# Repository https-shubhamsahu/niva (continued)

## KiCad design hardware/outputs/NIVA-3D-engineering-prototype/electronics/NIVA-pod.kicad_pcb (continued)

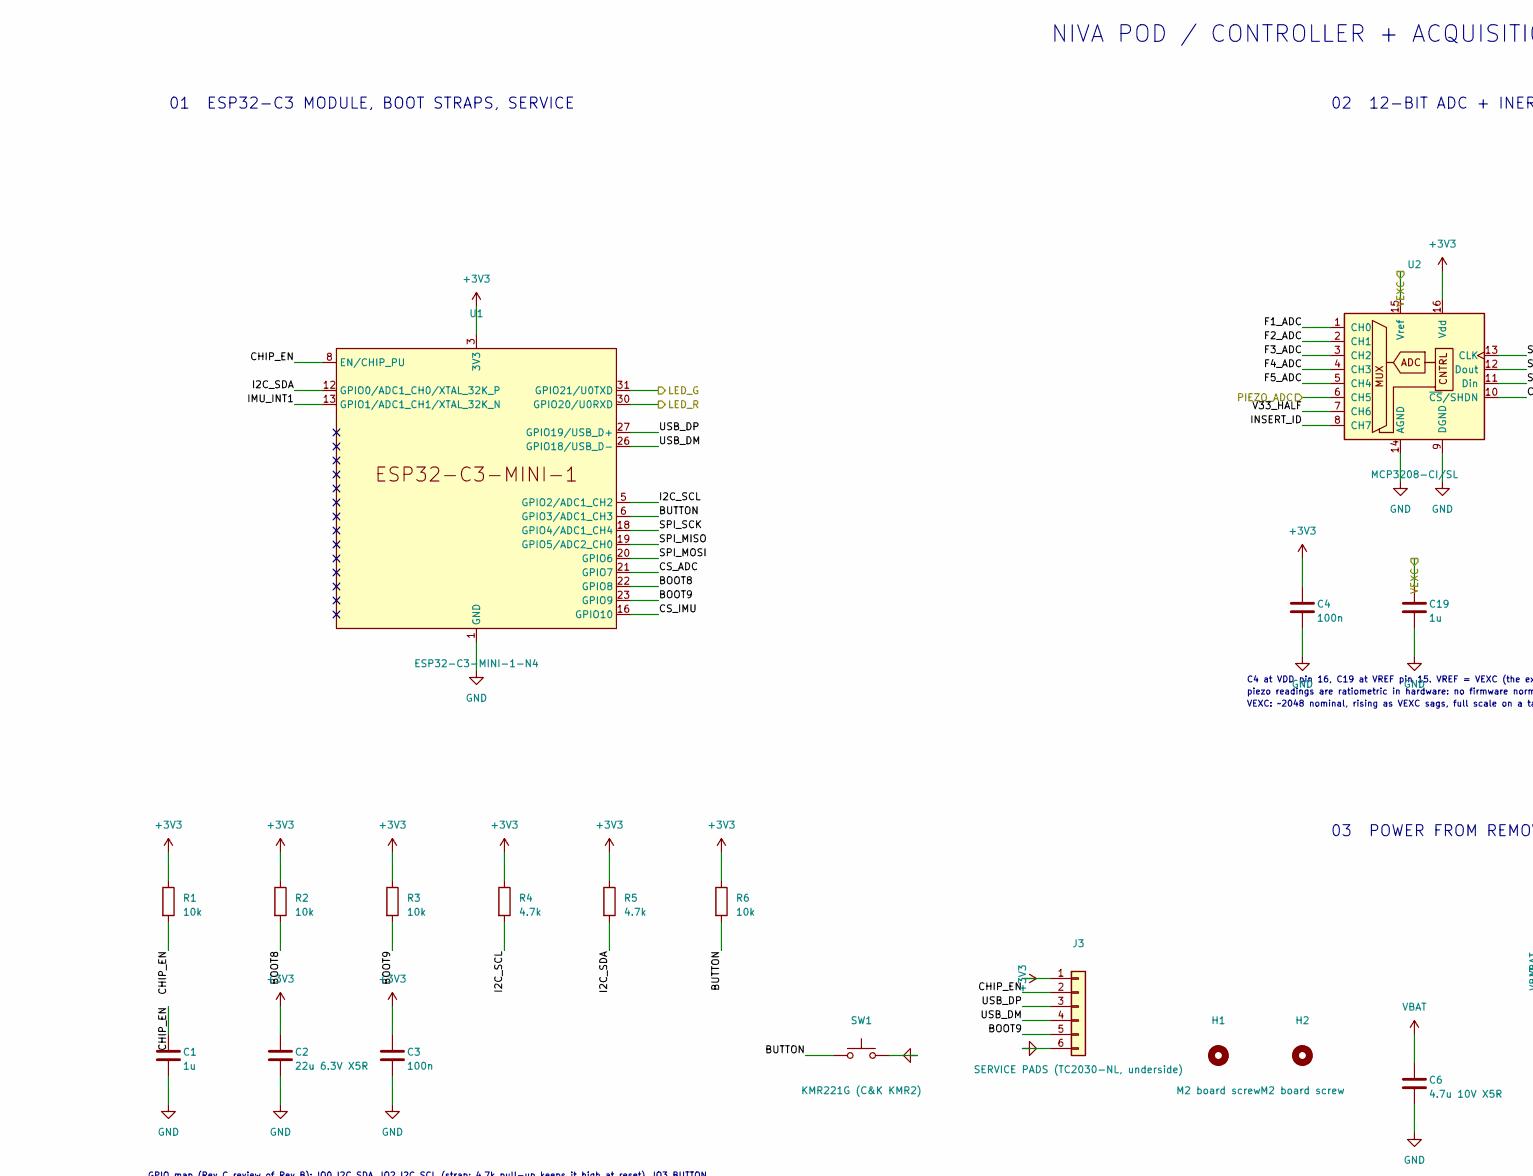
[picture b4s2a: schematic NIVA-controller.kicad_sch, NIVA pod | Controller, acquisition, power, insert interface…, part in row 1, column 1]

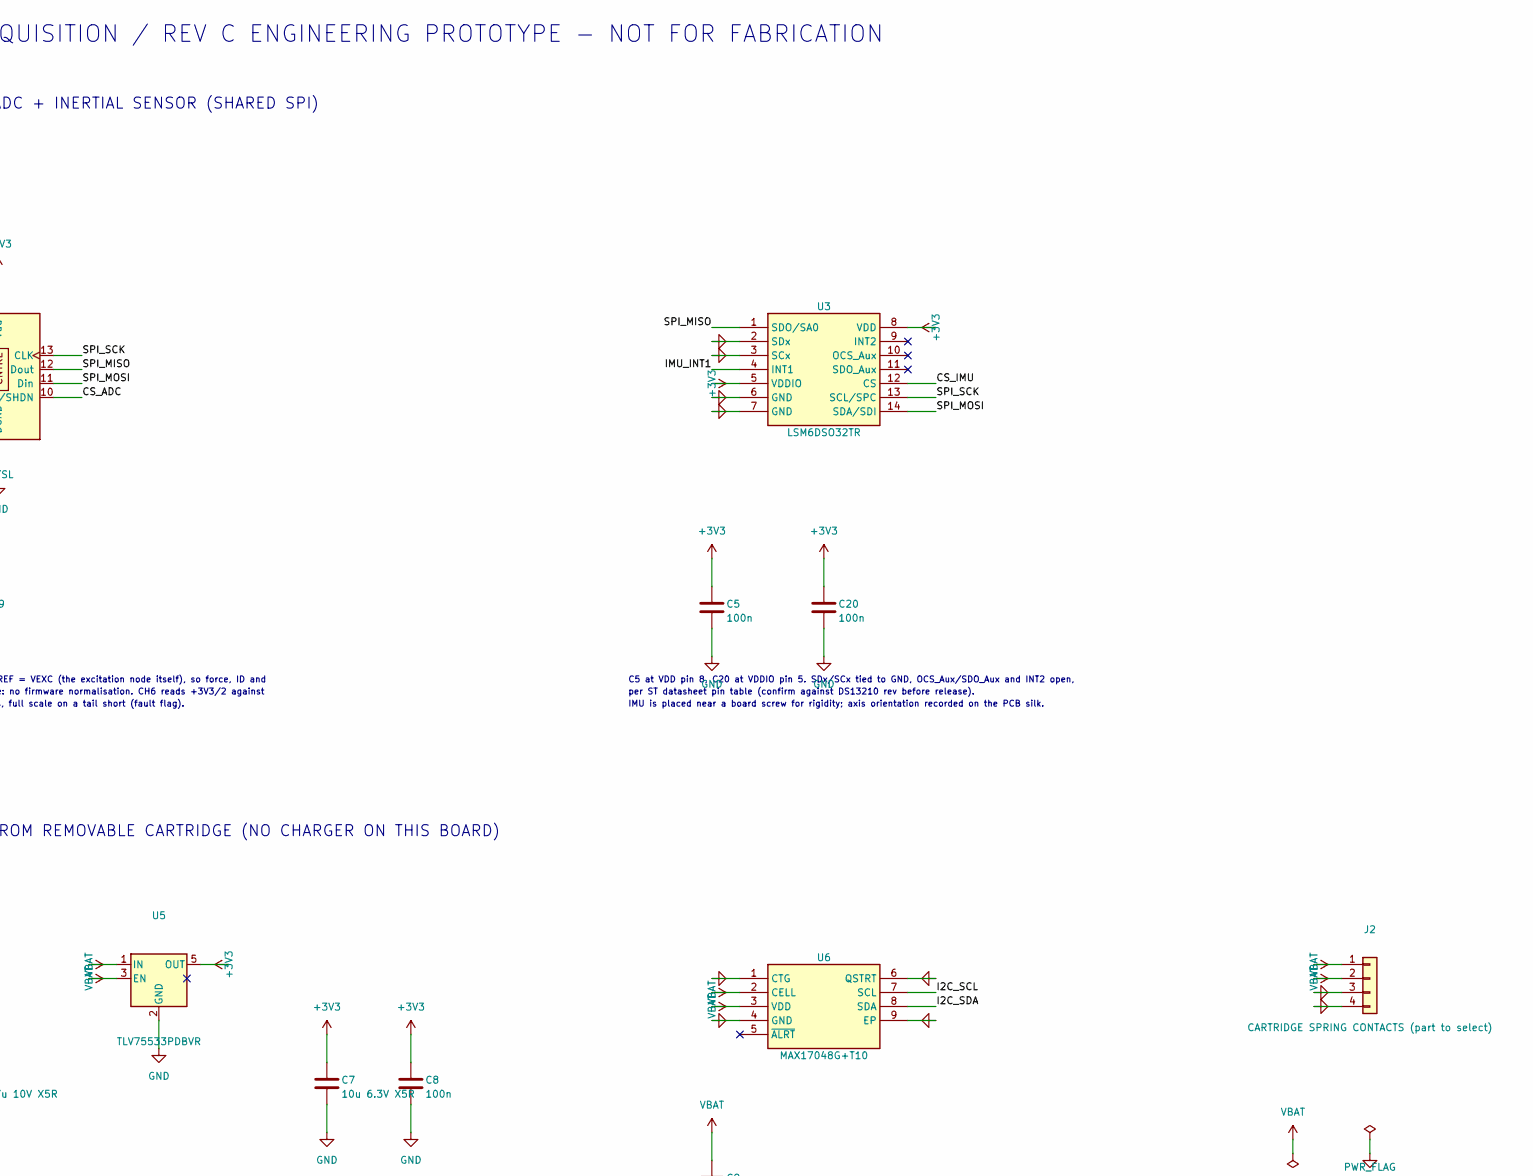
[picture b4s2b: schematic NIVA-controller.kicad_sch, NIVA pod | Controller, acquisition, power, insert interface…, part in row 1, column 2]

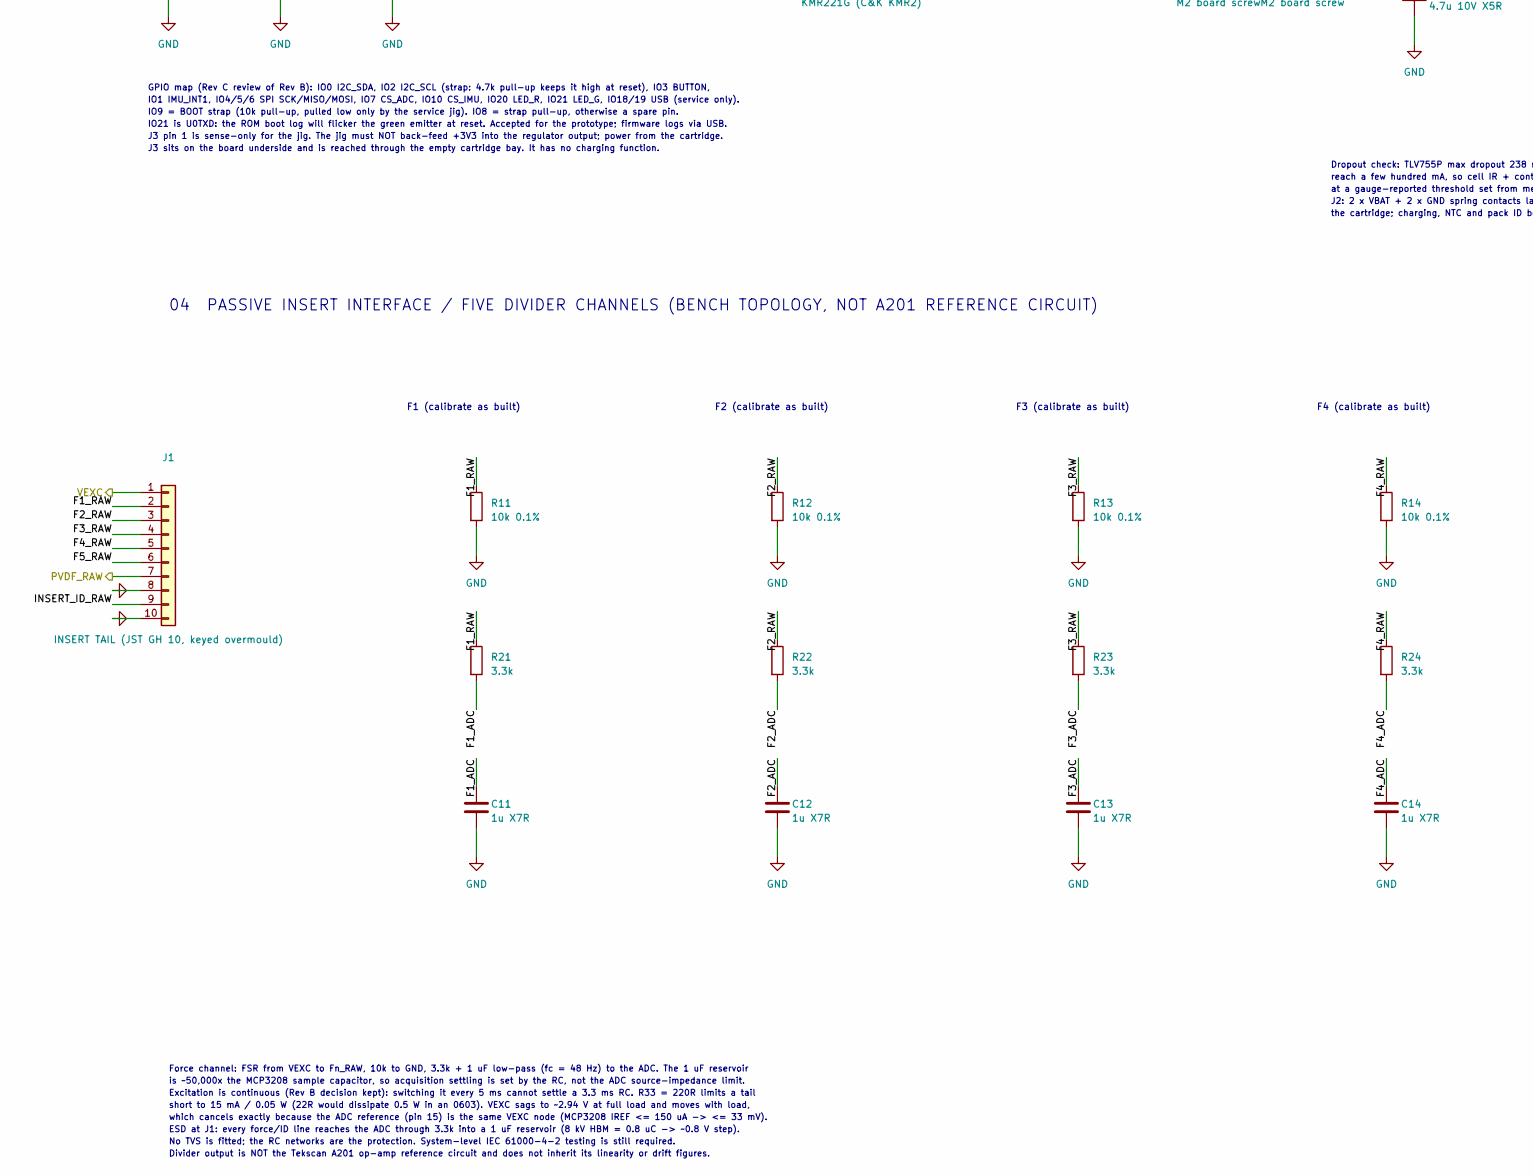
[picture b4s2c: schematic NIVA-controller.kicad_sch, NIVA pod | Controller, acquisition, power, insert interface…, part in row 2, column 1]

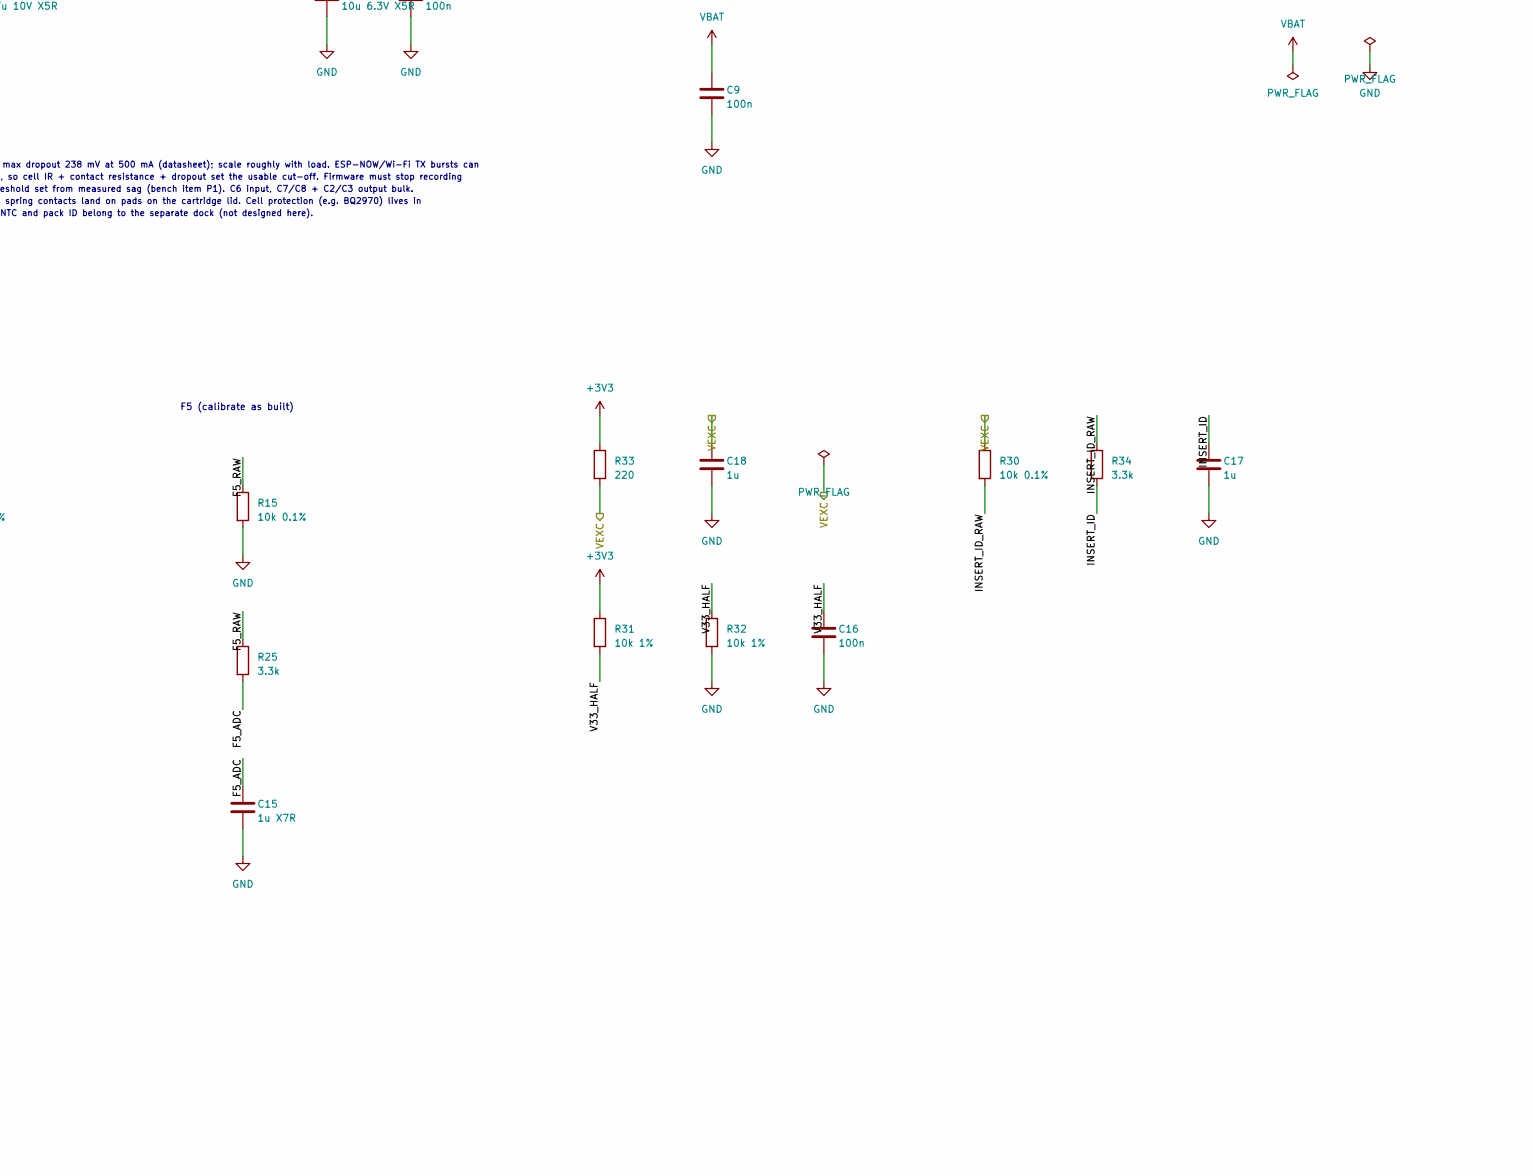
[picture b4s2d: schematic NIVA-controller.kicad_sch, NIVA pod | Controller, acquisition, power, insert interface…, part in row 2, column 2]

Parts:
C1, C17, C18, C19: 1u; C_0603_1608Metric
C2: 22u 6.3V X5R; C_0805_2012Metric
C3, C4, C5, C8, C9, C16, C20: 100n; C_0603_1608Metric
C6: 4.7u 10V X5R; C_0603_1608Metric
C7: 10u 6.3V X5R; C_0603_1608Metric
C11, C12, C13, C14, C15: 1u X7R; C_0603_1608Metric
H1, H2: M2 board screw; MountingHole_2.2mm_M2
J1: INSERT TAIL (JST GH 10, keyed overmould); JST_GH_SM10B-GHS-TB_1x10-1MP_P1.25mm_Horizontal; MPN SM10B-GHS-TB
J2: CARTRIDGE SPRING CONTACTS (part to select); SpringContact_1x04_P2.54mm_Vertical_SMD
J3: SERVICE PADS (TC2030-NL, underside); Tag-Connect_TC2030-IDC-NL_2x03_P1.27mm_Vertical
R1, R2, R3, R6: 10k; R_0603_1608Metric
R4, R5: 4.7k; R_0603_1608Metric
R11, R12, R13, R14, R15, R30: 10k 0.1%; R_0603_1608Metric
R21, R22, R23, R24, R25, R34: 3.3k; R_0603_1608Metric
R31, R32: 10k 1%; R_0603_1608Metric
R33: 220; R_0603_1608Metric
SW1: KMR221G (C&K KMR2); SW_Push_1P1T_NO_CK_KMR2
U1: ESP32-C3-MINI-1-N4; ESP32-C3-MINI-1; MPN ESP32-C3-MINI-1-N4
U2: MCP3208-CI/SL; SOIC-16_3.9x9.9mm_P1.27mm; MPN MCP3208-CI/SL
U3: LSM6DSO32TR; LGA-14_3x2.5mm_P0.5mm_LayoutBorder3x4y; MPN LSM6DSO32TR
U5: TLV75533PDBVR; SOT-23-5; MPN TLV75533PDBVR
U6: MAX17048G+T10; TDFN-8-1EP_2x2mm_P0.5mm_EP0.8x1.2mm; MPN MAX17048G+T10

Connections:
+3V3: C2.1, C3.1, C4.1, C5.1, C7.1, C8.1, C20.1, J3.1, R1.1, R2.1, R3.1, R4.1, R5.1, R6.1, R31.1, R33.1, U1.3 (3V3), U2.16 (Vdd), U3.5 (VDDIO), U3.8 (VDD), U5.5 (OUT); also elsewhere on the board
/Controller/BOOT8: R2.2, U1.22 (GPIO8)
/Controller/BOOT9: J3.5, R3.2, U1.23 (GPIO9)
/Controller/BUTTON: R6.2, SW1.1, U1.6 (GPIO3/ADC1_CH3)
/Controller/CHIP_EN: C1.1, J3.2, R1.2, U1.8 (EN/CHIP_PU)
/Controller/CS_ADC: U1.21 (GPIO7), U2.10 (~CS/SHDN)
/Controller/CS_IMU: U1.16 (GPIO10), U3.12 (CS)
/Controller/F1_ADC: C11.1, R21.2, U2.1 (CH0)
/Controller/F1_RAW: J1.2, R11.1, R21.1
/Controller/F2_ADC: C12.1, R22.2, U2.2 (CH1)
/Controller/F2_RAW: J1.3, R12.1, R22.1
/Controller/F3_ADC: C13.1, R23.2, U2.3 (CH2)
/Controller/F3_RAW: J1.4, R13.1, R23.1
/Controller/F4_ADC: C14.1, R24.2, U2.4 (CH3)
/Controller/F4_RAW: J1.5, R14.1, R24.1
/Controller/F5_ADC: C15.1, R25.2, U2.5 (CH4)
/Controller/F5_RAW: J1.6, R15.1, R25.1
/Controller/I2C_SCL: R4.2, U1.5 (GPIO2/ADC1_CH2), U6.7 (SCL)
/Controller/I2C_SDA: R5.2, U1.12 (GPIO0/ADC1_CH0/XTAL_32K_P), U6.8 (SDA)
/Controller/IMU_INT1: U1.13 (GPIO1/ADC1_CH1/XTAL_32K_N), U3.4 (INT1)
/Controller/INSERT_ID: C17.1, R34.2, U2.8 (CH7)
/Controller/INSERT_ID_RAW: J1.9, R30.2, R34.1
/Controller/LED_G: U1.31 (GPIO21/U0TXD); also elsewhere on the board
/Controller/LED_R: U1.30 (GPIO20/U0RXD); also elsewhere on the board
/Controller/PIEZO_ADC: U2.6 (CH5); also elsewhere on the board
/Controller/PVDF_RAW: J1.7; also elsewhere on the board
/Controller/SPI_MISO: U1.19 (GPIO5/ADC2_CH0), U2.12 (Dout), U3.1 (SDO/SA0)
/Controller/SPI_MOSI: U1.20 (GPIO6), U2.11 (Din), U3.14 (SDA/SDI)
/Controller/SPI_SCK: U1.18 (GPIO4/ADC1_CH4), U2.13 (CLK), U3.13 (SCL/SPC)
/Controller/USB_DM: J3.4, U1.26 (GPIO18/USB_D-)
/Controller/USB_DP: J3.3, U1.27 (GPIO19/USB_D+)
/Controller/V33_HALF: C16.1, R31.2, R32.1, U2.7 (CH6)
/Controller/VEXC: C18.1, C19.1, J1.1, R30.1, R33.2, U2.15 (Vref); also elsewhere on the board
GND: C1.2, C2.2, C3.2, C4.2, C5.2, C6.2, C7.2, C8.2, C9.2, C11.2, C12.2, C13.2, C14.2, C15.2, C16.2, C17.2, C18.2, C19.2, C20.2, J1.8, J1.10, J2.3, J2.4, J3.6, R11.2, R12.2, R13.2, R14.2, R15.2, R32.2, SW1.2, U1.1 (GND), U1.2 (GND), U1.11 (GND), U1.14 (GND), U1.36 (GND), U1.37 (GND), U1.38 (GND), U1.39 (GND), U1.40 (GND), U1.41 (GND), U1.42 (GND), U1.43 (GND), U1.44 (GND), U1.45 (GND), U1.46 (GND), U1.47 (GND), U1.48 (GND), U1.49 (GND), U1.50 (GND), U1.51 (GND), U1.52 (GND), U1.53 (GND), U2.9 (DGND), U2.14 (AGND), U3.2 (SDx), U3.3 (SCx), U3.6 (GND), U3.7 (GND), U5.2 (GND), U6.1 (CTG), U6.4 (GND), U6.6 (QSTRT), U6.9 (EP); also elsewhere on the board
VBAT: C6.1, C9.1, J2.1, J2.2, U5.1 (IN), U5.3 (EN), U6.2 (CELL), U6.3 (VDD)

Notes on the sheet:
NIVA POD / CONTROLLER + ACQUISITION / REV C ENGINEERING PROTOTYPE - NOT FOR FABRICATION
01 ESP32-C3 MODULE, BOOT STRAPS, SERVICE
GPIO map (Rev C review of Rev B): IO0 I2C_SDA, IO2 I2C_SCL (strap: 4.7k pull-up keeps it high at reset), IO3 BUTTON,
IO1 IMU_INT1, IO4/5/6 SPI SCK/MISO/MOSI, IO7 CS_ADC, IO10 CS_IMU, IO20 LED_R, IO21 LED_G, IO18/19 USB (service only).
IO9 = BOOT strap (10k pull-up, pulled low only by the service jig). IO8 = strap pull-up, otherwise a spare pin.
IO21 is U0TXD: the ROM boot log will flicker the green emitter at reset. Accepted for the prototype; firmware logs via USB.
J3 pin 1 is sense-only for the jig. The jig must NOT back-feed +3V3 into the regulator output; power from the cartridge.
J3 sits on the board underside and is reached through the empty cartridge bay. It has no charging function.
02 12-BIT ADC + INERTIAL SENSOR (SHARED SPI)
C4 at VDD pin 16, C19 at VREF pin 15. VREF = VEXC (the excitation node itself), so force, ID and
piezo readings are ratiometric in hardware: no firmware normalisation. CH6 reads +3V3/2 against
VEXC: ~2048 nominal, rising as VEXC sags, full scale on a tail short (fault flag).
C5 at VDD pin 8, C20 at VDDIO pin 5. SDx/SCx tied to GND, OCS_Aux/SDO_Aux and INT2 open,
per ST datasheet pin table (confirm against DS13210 rev before release).
IMU is placed near a board screw for rigidity; axis orientation recorded on the PCB silk.
03 POWER FROM REMOVABLE CARTRIDGE (NO CHARGER ON THIS BOARD)
Dropout check: TLV755P max dropout 238 mV at 500 mA (datasheet); scale roughly with load. ESP-NOW/Wi-Fi TX bursts can
reach a few hundred mA, so cell IR + contact resistance + dropout set the usable cut-off. Firmware must stop recording
at a gauge-reported threshold set from measured sag (bench item P1). C6 input, C7/C8 + C2/C3 output bulk.
J2: 2 x VBAT + 2 x GND spring contacts land on pads on the cartridge lid. Cell protection (e.g. BQ2970) lives in
the cartridge; charging, NTC and pack ID belong to the separate dock (not designed here).
04 PASSIVE INSERT INTERFACE / FIVE DIVIDER CHANNELS (BENCH TOPOLOGY, NOT A201 REFERENCE CIRCUIT)
F1 (calibrate as built)
F2 (calibrate as built)
F3 (calibrate as built)
F4 (calibrate as built)
F5 (calibrate as built)
Force channel: FSR from VEXC to Fn_RAW, 10k to GND, 3.3k + 1 uF low-pass (fc = 48 Hz) to the ADC. The 1 uF reservoir
is ~50,000x the MCP3208 sample capacitor, so acquisition settling is set by the RC, not the ADC source-impedance limit.
Excitation is continuous (Rev B decision kept): switching it every 5 ms cannot settle a 3.3 ms RC. R33 = 220R limits a tail
short to 15 mA / 0.05 W (22R would dissipate 0.5 W in an 0603). VEXC sags to ~2.94 V at full load and moves with load,
which cancels exactly because the ADC reference (pin 15) is the same VEXC node (MCP3208 IREF <= 150 uA -> <= 33 mV).
ESD at J1: every force/ID line reaches the ADC through 3.3k into a 1 uF reservoir (8 kV HBM = 0.8 uC -> ~0.8 V step).
No TVS is fitted; the RC networks are the protection. System-level IEC 61000-4-2 testing is still required.
Divider output is NOT the Tekscan A201 op-amp reference circuit and does not inherit its linearity or drift figures.

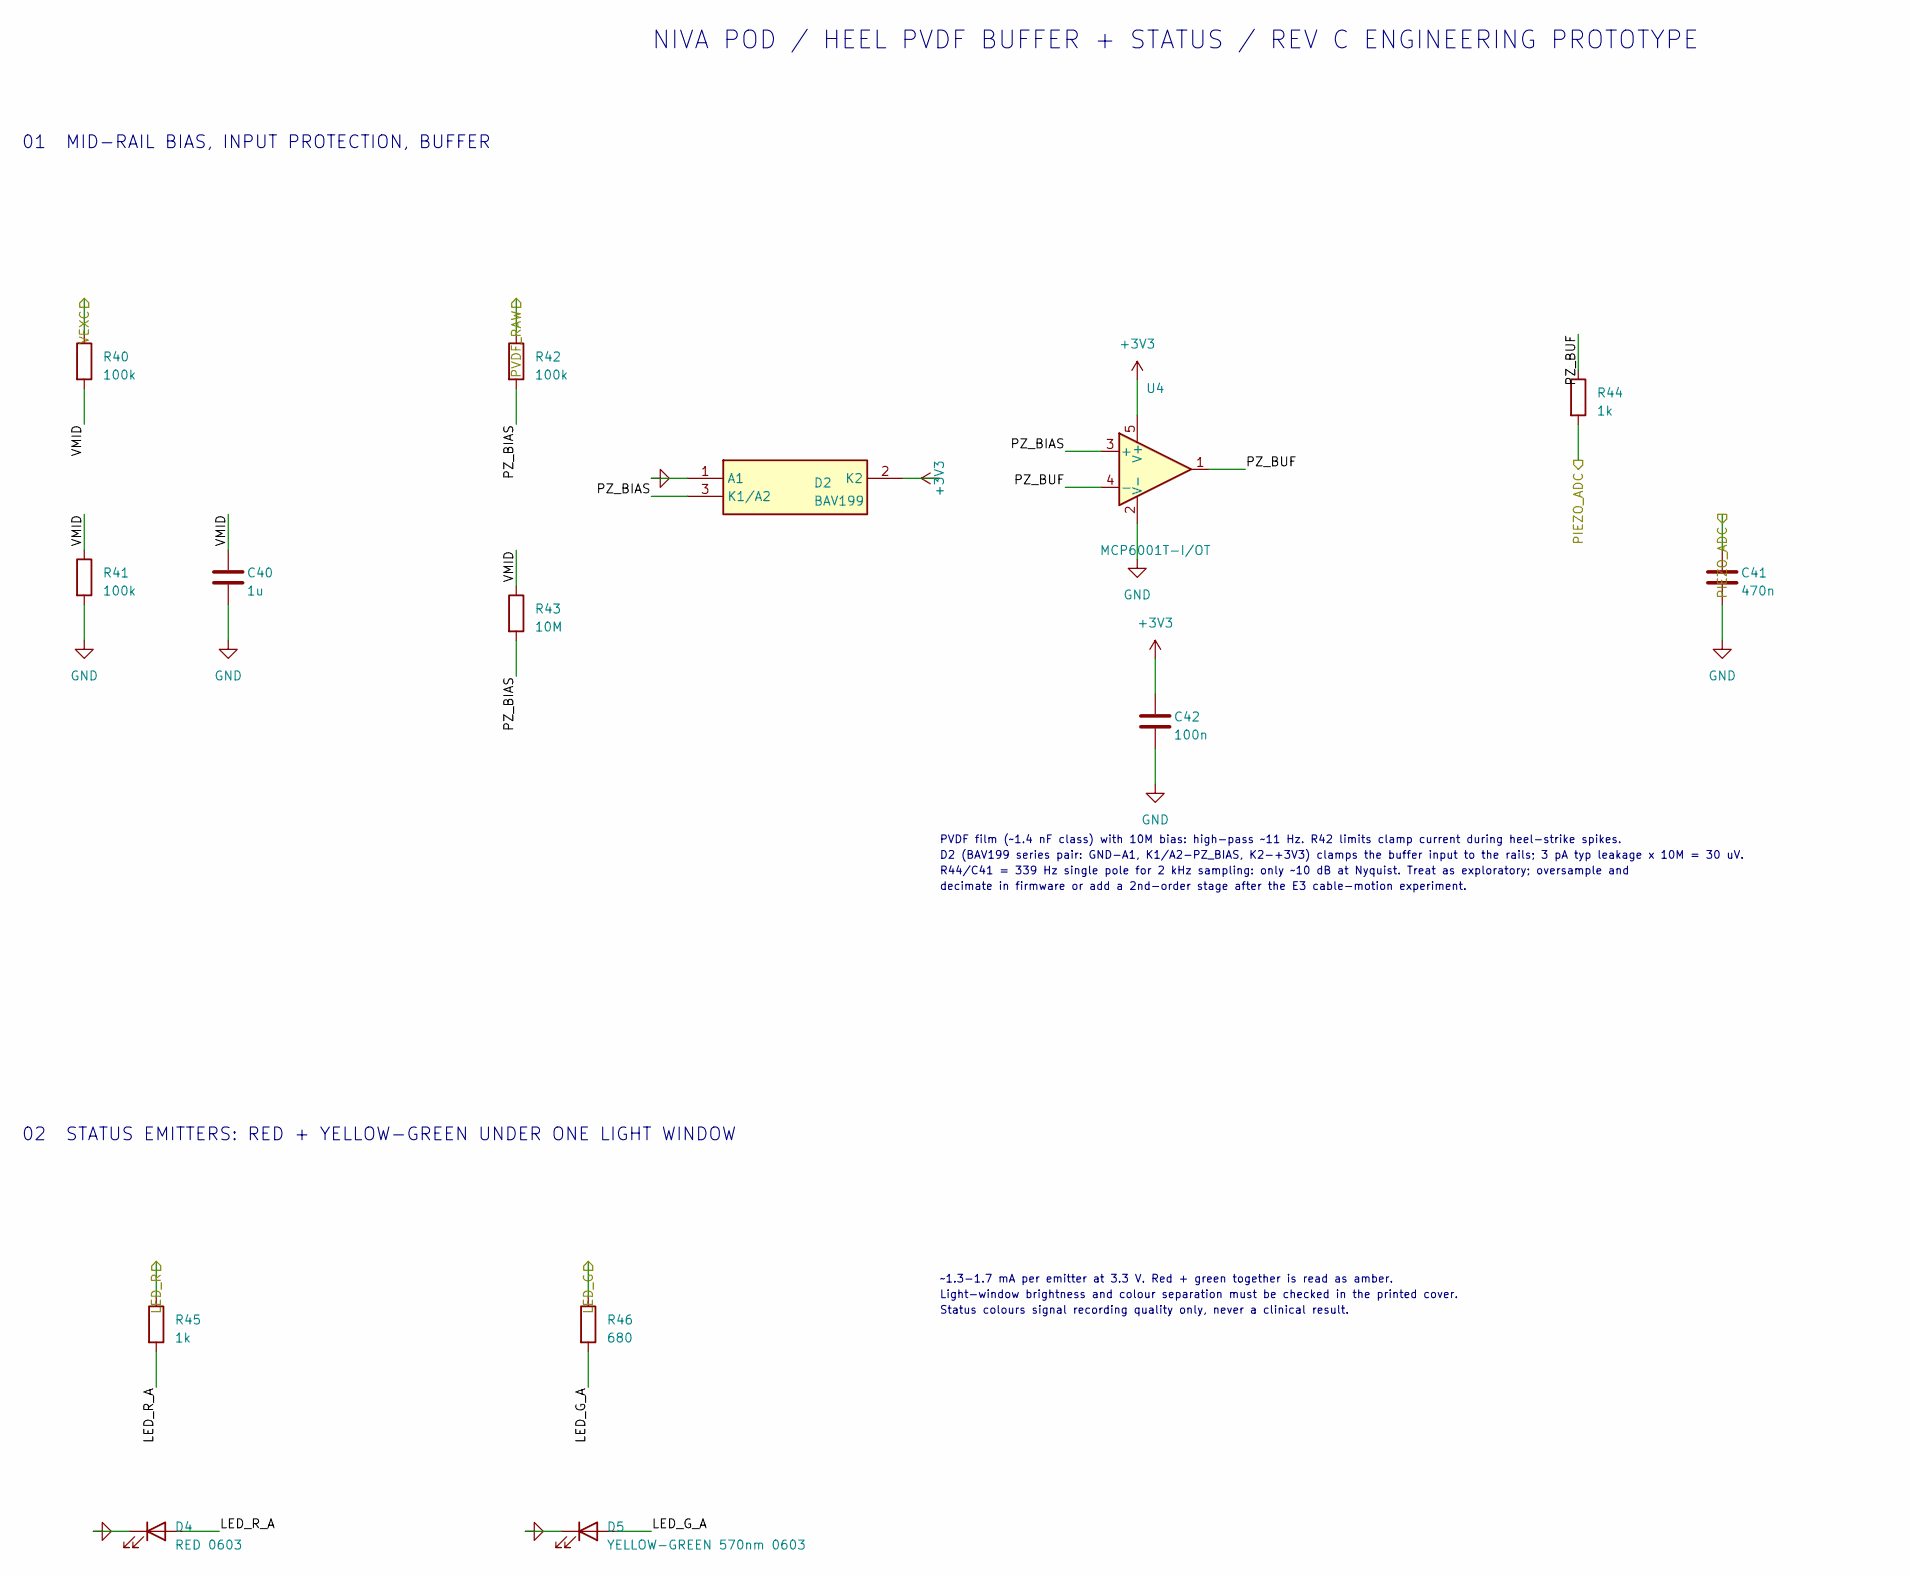
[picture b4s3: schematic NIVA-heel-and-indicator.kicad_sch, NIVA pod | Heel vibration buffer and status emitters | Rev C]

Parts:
C40: 1u; C_0603_1608Metric
C41: 470n; C_0603_1608Metric
C42: 100n; C_0603_1608Metric
D2: BAV199; SOT-23; MPN BAV199,215 (Nexperia) low-leakage serie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
D4: RED 0603; LED_0603_1608Metric
D5: YELLOW-GREEN 570nm 0603; LED_0603_1608Metric
R40, R41, R42: 100k; R_0603_1608Metric
R43: 10M; R_0603_1608Metric
R44, R45: 1k; R_0603_1608Metric
R46: 680; R_0603_1608Metric
U4: MCP6001T-I/OT; SOT-23-5; MPN MCP6001T-I/OT

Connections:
+3V3: C42.1, D2.2 (K2), U4.5 (V+); also elsewhere on the board
/Controller/LED_G: R46.1; also elsewhere on the board
/Controller/LED_R: R45.1; also elsewhere on the board
/Controller/PIEZO_ADC: C41.1, R44.2; also elsewhere on the board
/Controller/PVDF_RAW: R42.1; also elsewhere on the board
/Controller/VEXC: R40.1; also elsewhere on the board
/Heel and indicator/LED_G_A: D5.2 (A), R46.2
/Heel and indicator/LED_R_A: D4.2 (A), R45.2
/Heel and indicator/PZ_BIAS: D2.3 (K1/A2), R42.2, R43.2, U4.3 (+)
/Heel and indicator/PZ_BUF: R44.1, U4.1, U4.4 (-)
/Heel and indicator/VMID: C40.1, R40.2, R41.1, R43.1
GND: C40.2, C41.2, C42.2, D2.1 (A1), D4.1 (K), D5.1 (K), R41.2, U4.2 (V-); also elsewhere on the board

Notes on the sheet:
NIVA POD / HEEL PVDF BUFFER + STATUS / REV C ENGINEERING PROTOTYPE
01 MID-RAIL BIAS, INPUT PROTECTION, BUFFER
PVDF film (~1.4 nF class) with 10M bias: high-pass ~11 Hz. R42 limits clamp current during heel-strike spikes.
D2 (BAV199 series pair: GND-A1, K1/A2-PZ_BIAS, K2-+3V3) clamps the buffer input to the rails; 3 pA typ leakage x 10M = 30 uV.
R44/C41 = 339 Hz single pole for 2 kHz sampling: only ~10 dB at Nyquist. Treat as exploratory; oversample and
decimate in firmware or add a 2nd-order stage after the E3 cable-motion experiment.
02 STATUS EMITTERS: RED + YELLOW-GREEN UNDER ONE LIGHT WINDOW
~1.3-1.7 mA per emitter at 3.3 V. Red + green together is read as amber.
Light-window brightness and colour separation must be checked in the printed cover.
Status colours signal recording quality only, never a clinical result.

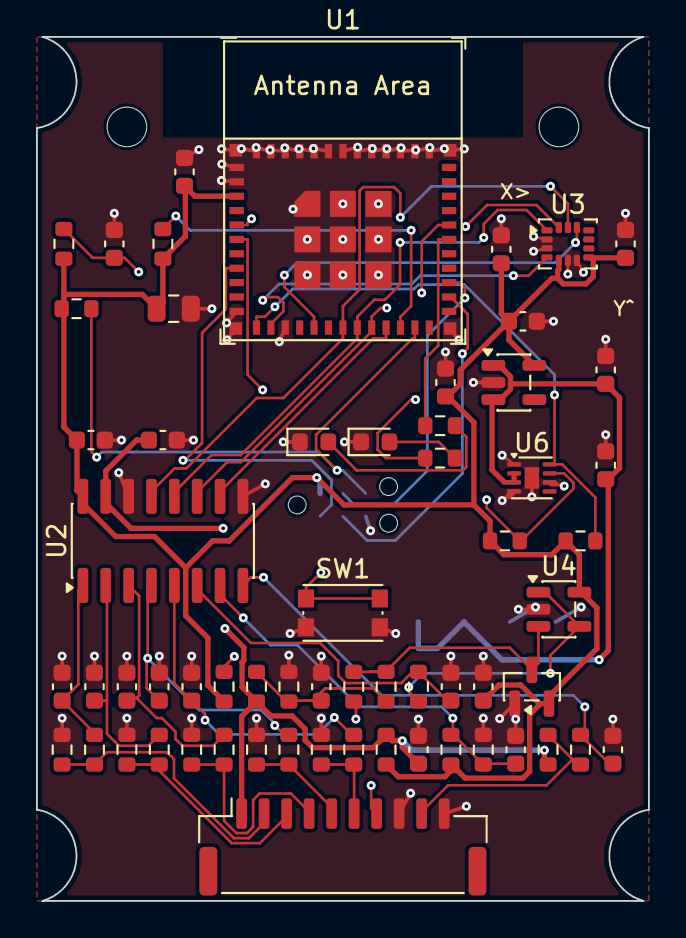
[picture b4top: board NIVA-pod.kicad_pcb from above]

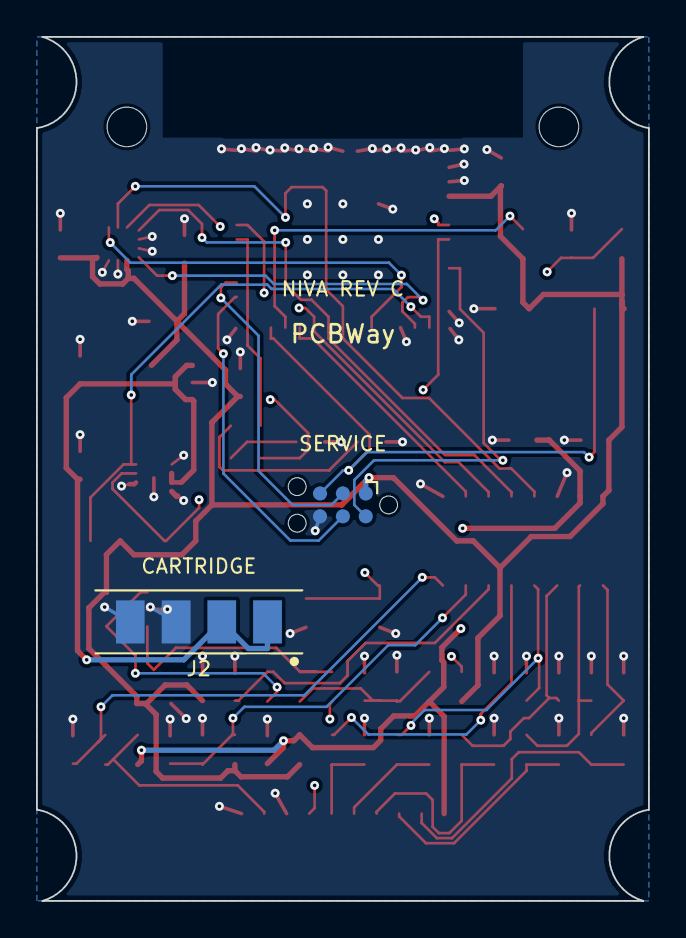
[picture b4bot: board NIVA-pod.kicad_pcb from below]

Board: 4 copper layers, 34.0 x 48.0 mm, 65 parts (2 on the bottom side), 40 nets.

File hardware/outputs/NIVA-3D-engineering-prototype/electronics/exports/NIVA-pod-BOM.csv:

"Reference","Value","Footprint","MPN","QUANTITY"
"C1,C17-C19,C40","1u","Capacitor_SMD:C_0603_1608Metric","","5"
"C2","22u 6.3V X5R","Capacitor_SMD:C_0805_2012Metric","","1"
"C3-C5,C8,C9,C16,C20,C42","100n","Capacitor_SMD:C_0603_1608Metric","","8"
"C6","4.7u 10V X5R","Capacitor_SMD:C_0603_1608Metric","","1"
"C7","10u 6.3V X5R","Capacitor_SMD:C_0603_1608Metric","","1"
"C11-C15","1u X7R","Capacitor_SMD:C_0603_1608Metric","","5"
"C41","470n","Capacitor_SMD:C_0603_1608Metric","","1"
"D2","BAV199","Package_TO_SOT_SMD:SOT-23","BAV199,215 (Nexperia) low-leakage series pair, SOT-23","1"
"D4","RED 0603","LED_SMD:LED_0603_1608Metric","","1"
"D5","YELLOW-GREEN 570nm 0603","LED_SMD:LED_0603_1608Metric","","1"
"J1","INSERT TAIL (JST GH 10, keyed overmould)","Connector_JST:JST_GH_SM10B-GHS-TB_1x10-1MP_P1.25mm_Horizontal","SM10B-GHS-TB","1"
"J2","CARTRIDGE SPRING CONTACTS (part to select)","NIVA:SpringContact_1x04_P2.54mm_Vertical_SMD","","1"
"R1-R3,R6","10k","Resistor_SMD:R_0603_1608Metric","","4"
"R4,R5","4.7k","Resistor_SMD:R_0603_1608Metric","","2"
"R11-R15,R30","10k 0.1%","Resistor_SMD:R_0603_1608Metric","","6"
"R21-R25,R34","3.3k","Resistor_SMD:R_0603_1608Metric","","6"
"R31,R32","10k 1%","Resistor_SMD:R_0603_1608Metric","","2"
"R33","220","Resistor_SMD:R_0603_1608Metric","","1"
"R40-R42","100k","Resistor_SMD:R_0603_1608Metric","","3"
"R43","10M","Resistor_SMD:R_0603_1608Metric","","1"
"R44,R45","1k","Resistor_SMD:R_0603_1608Metric","","2"
"R46","680","Resistor_SMD:R_0603_1608Metric","","1"
"SW1","KMR221G (C&K KMR2)","Button_Switch_SMD:SW_Push_1P1T_NO_CK_KMR2","","1"
"U1","ESP32-C3-MINI-1-N4","NIVA:ESP32-C3-MINI-1","ESP32-C3-MINI-1-N4","1"
"U2","MCP3208-CI/SL","Package_SO:SOIC-16_3.9x9.9mm_P1.27mm","MCP3208-CI/SL","1"
"U3","LSM6DSO32TR","Package_LGA:LGA-14_3x2.5mm_P0.5mm_LayoutBorder3x4y","LSM6DSO32TR","1"
"U4","MCP6001T-I/OT","Package_TO_SOT_SMD:SOT-23-5","MCP6001T-I/OT","1"
"U5","TLV75533PDBVR","Package_TO_SOT_SMD:SOT-23-5","TLV75533PDBVR","1"
"U6","MAX17048G+T10","Package_DFN_QFN:TDFN-8-1EP_2x2mm_P0.5mm_EP0.8x1.2mm","MAX17048G+T10","1"

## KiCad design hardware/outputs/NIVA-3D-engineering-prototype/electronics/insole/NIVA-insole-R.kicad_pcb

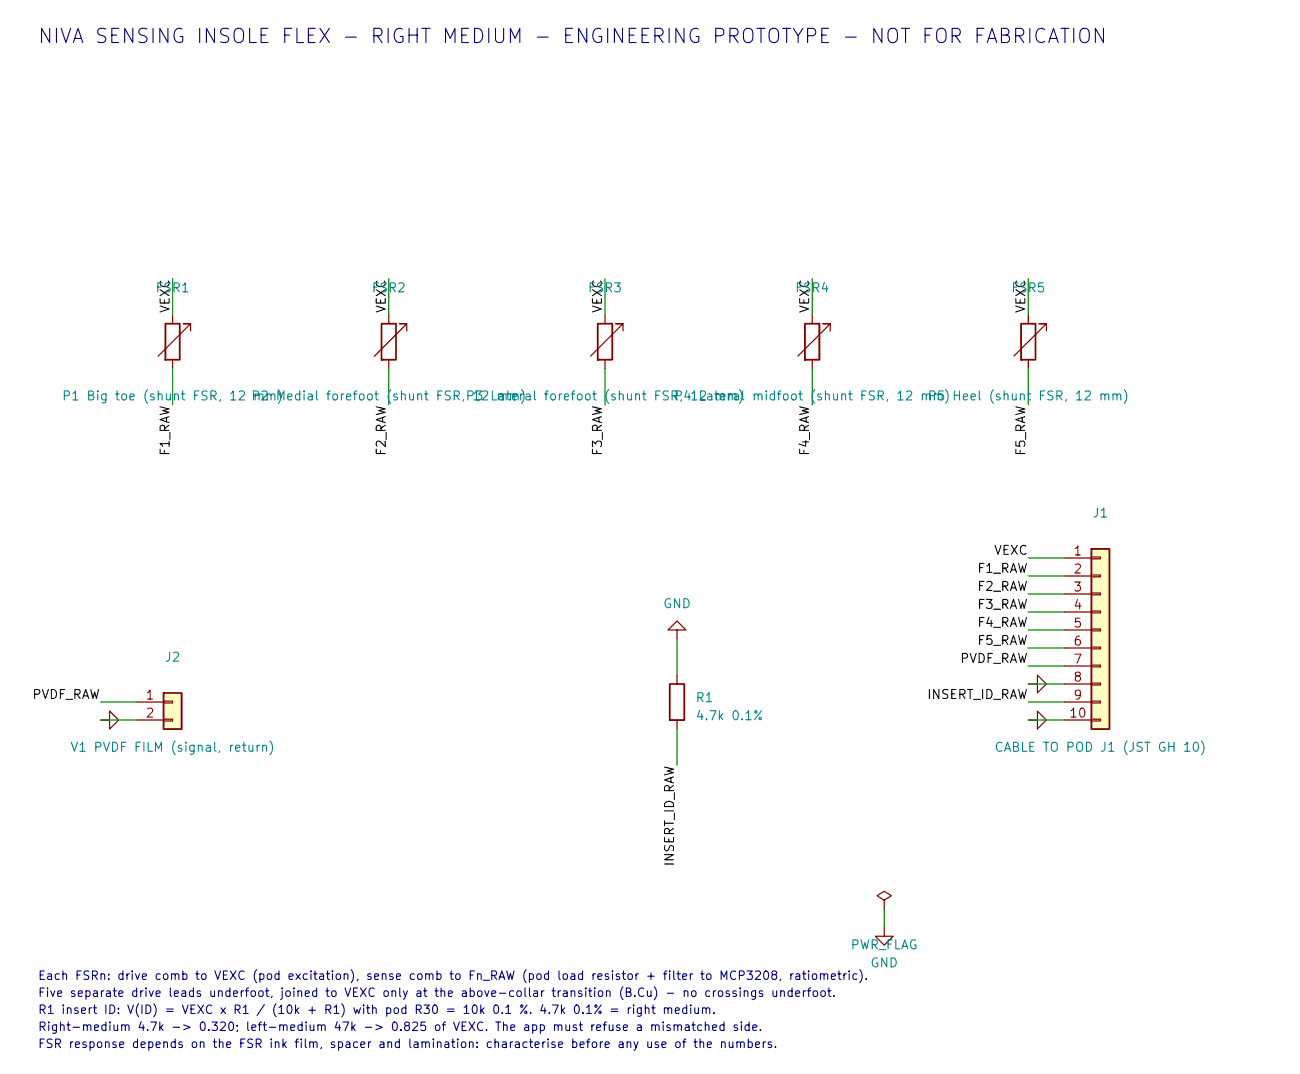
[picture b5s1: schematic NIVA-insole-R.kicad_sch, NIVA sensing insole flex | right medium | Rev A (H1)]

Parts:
FSR1: P1 Big toe (shunt FSR, 12 mm); FSR_Interdigitated_D12mm
FSR2: P2 Medial forefoot (shunt FSR, 12 mm); FSR_Interdigitated_D12mm
FSR3: P3 Lateral forefoot (shunt FSR, 12 mm); FSR_Interdigitated_D12mm
FSR4: P4 Lateral midfoot (shunt FSR, 12 mm); FSR_Interdigitated_D12mm
FSR5: P5 Heel (shunt FSR, 12 mm); FSR_Interdigitated_D12mm
J1: CABLE TO POD J1 (JST GH 10); WirePads_1x10_P2.0mm_LaneOrder
J2: V1 PVDF FILM (signal, return); PVDF_BondPads_2x6x2mm
R1: 4.7k 0.1%; R_0603_1608Metric; MPN 0603 thin film 4.7k 0.1% (right medium 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

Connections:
/F1_RAW: FSR1.2, J1.2
/F2_RAW: FSR2.2, J1.3
/F3_RAW: FSR3.2, J1.4
/F4_RAW: FSR4.2, J1.5
/F5_RAW: FSR5.2, J1.6
/INSERT_ID_RAW: J1.9, R1.2
/PVDF_RAW: J1.7, J2.1
/VEXC: FSR1.1, FSR2.1, FSR3.1, FSR4.1, FSR5.1, J1.1
GND: J1.8, J1.10, J2.2, R1.1

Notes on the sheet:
NIVA SENSING INSOLE FLEX - RIGHT MEDIUM - ENGINEERING PROTOTYPE - NOT FOR FABRICATION
Each FSRn: drive comb to VEXC (pod excitation), sense comb to Fn_RAW (pod load resistor + filter to MCP3208, ratiometric).
Five separate drive leads underfoot, joined to VEXC only at the above-collar transition (B.Cu) - no crossings underfoot.
R1 insert ID: V(ID) = VEXC x R1 / (10k + R1) with pod R30 = 10k 0.1 %. 4.7k 0.1% = right medium.
Right-medium 4.7k -> 0.320; left-medium 47k -> 0.825 of VEXC. The app must refuse a mismatched side.
FSR response depends on the FSR ink film, spacer and lamination: characterise before any use of the numbers.

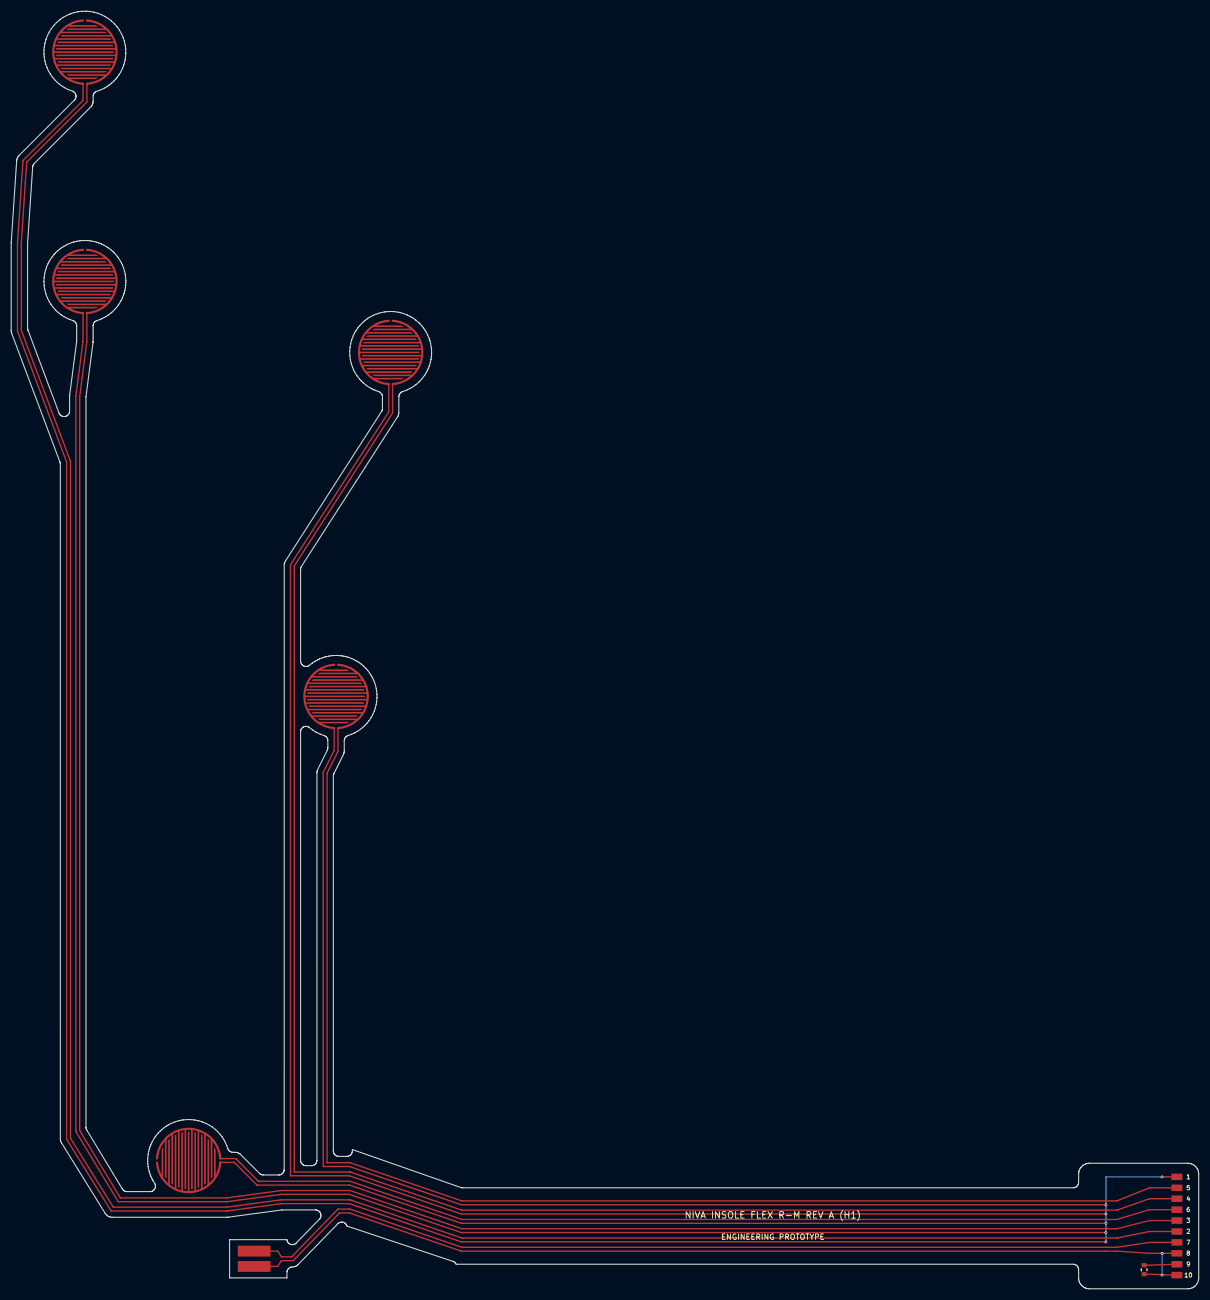
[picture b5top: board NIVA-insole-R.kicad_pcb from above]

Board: 2 copper layers, 217.5 x 234.0 mm, 8 parts (0 on the bottom side), 9 nets.

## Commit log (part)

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2026-03-14 readme add
2026-03-14 [ImgBot] Optimize images
    *Total -- 796.73kb -> 511.40kb (35.81%)
    /public/feet.png -- 755.16kb -> 471.29kb (37.59%)
    /public/architecture-diagram.svg -- 7.58kb -> 7.17kb (5.44%)
    /public/niva_logo.jpeg -- 33.99kb -> 32.95kb (3.07%)
2026-03-18 Configure GitHub Pages deployment
2026-03-18 Fix bilateral foot image path for GitHub Pages
2026-03-20 Add runtime ESP32 WiFi/hotspot endpoint configuration
2026-03-20 Enable seamless relay fallback for deployed ESP32 connectivity
2026-03-20 Add runtime relay endpoint input and stable relay routing
2026-03-20 Add default controls and low-noise zero-load calibration
2026-03-20 Simplify ESP32 hardcoded WiFi firmware
